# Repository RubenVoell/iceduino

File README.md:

# A ICE40HX4k Breakout for educational purposes

The basic idea behind this project is to create a simple breakout of an ICE40 FPGA with some LEDs and Buttons to interact with the FPGA and enough resources to run a simple softcore, like a small RISC-V core. Therefore a SRAM will be added in case the internal memory blocks are not big enough, The configuration SPI flash may be used to store programm data for the softcore. So this board can be used for teaching basic FPGA, microcontroller and CPU architecture topics.

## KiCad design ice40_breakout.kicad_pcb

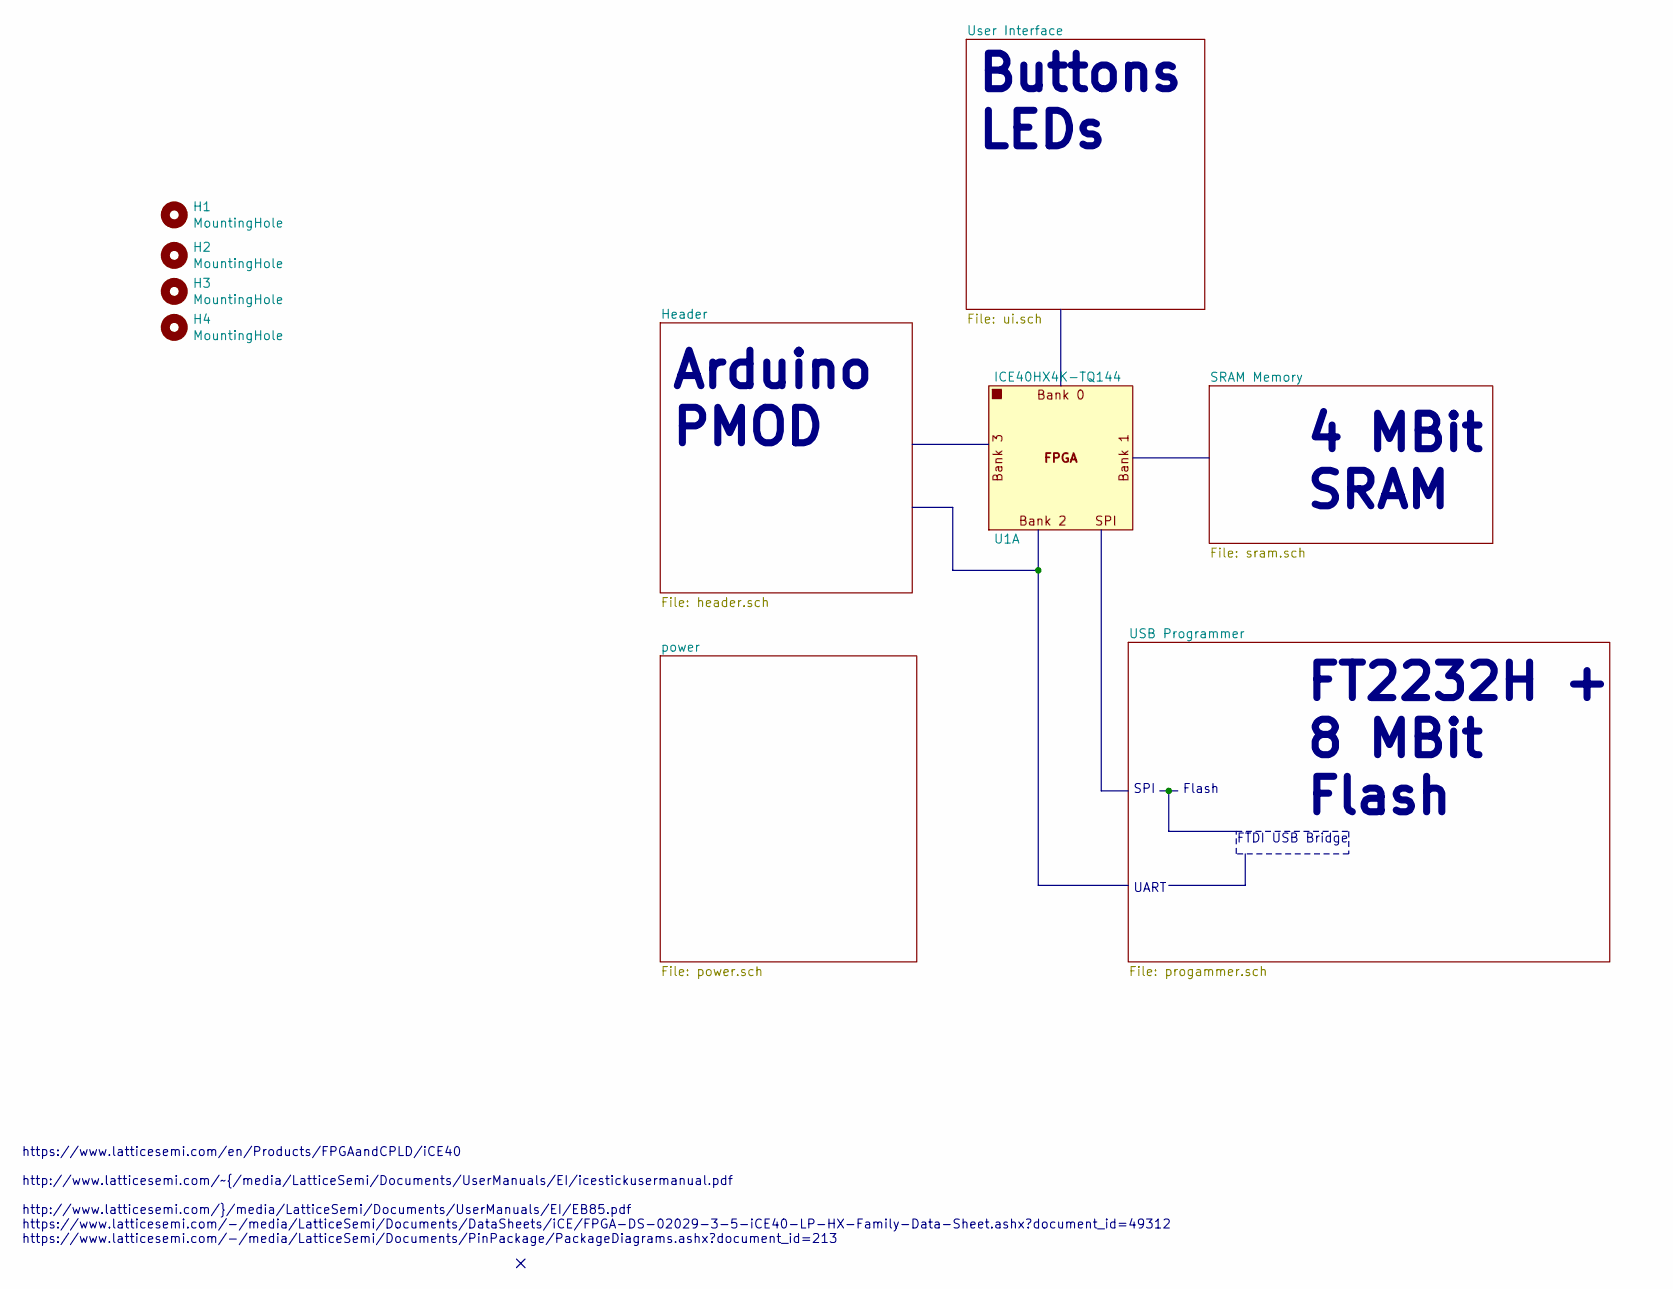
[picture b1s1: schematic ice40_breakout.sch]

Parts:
H1, H2, H3, H4: MountingHole; MountingHole_3mm
U1: ICE40HX4K-TQ144; TQFP-144_20x20mm_P0.5mm; Mfg Part Num ICE40HX4K-TQ144; Digikey 220-1572-ND

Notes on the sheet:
https://www.latticesemi.com/en/Products/FPGAandCPLD/iCE40 http://www.latticesemi.com/~/media/LatticeSemi/Documents/UserManuals/EI/icestickusermanual.pdf http://www.latticesemi.com/~/media/LatticeSemi/Documents/UserManuals/EI/EB85.pdf https://www.latticesemi.com/-/media/LatticeSemi/Documents/DataShe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
SPI
Flash
UART
FTDI USB Bridge
4 MBit SRAM
Arduino PMOD
Buttons LEDs
FT2232H + 8 MBit Flash

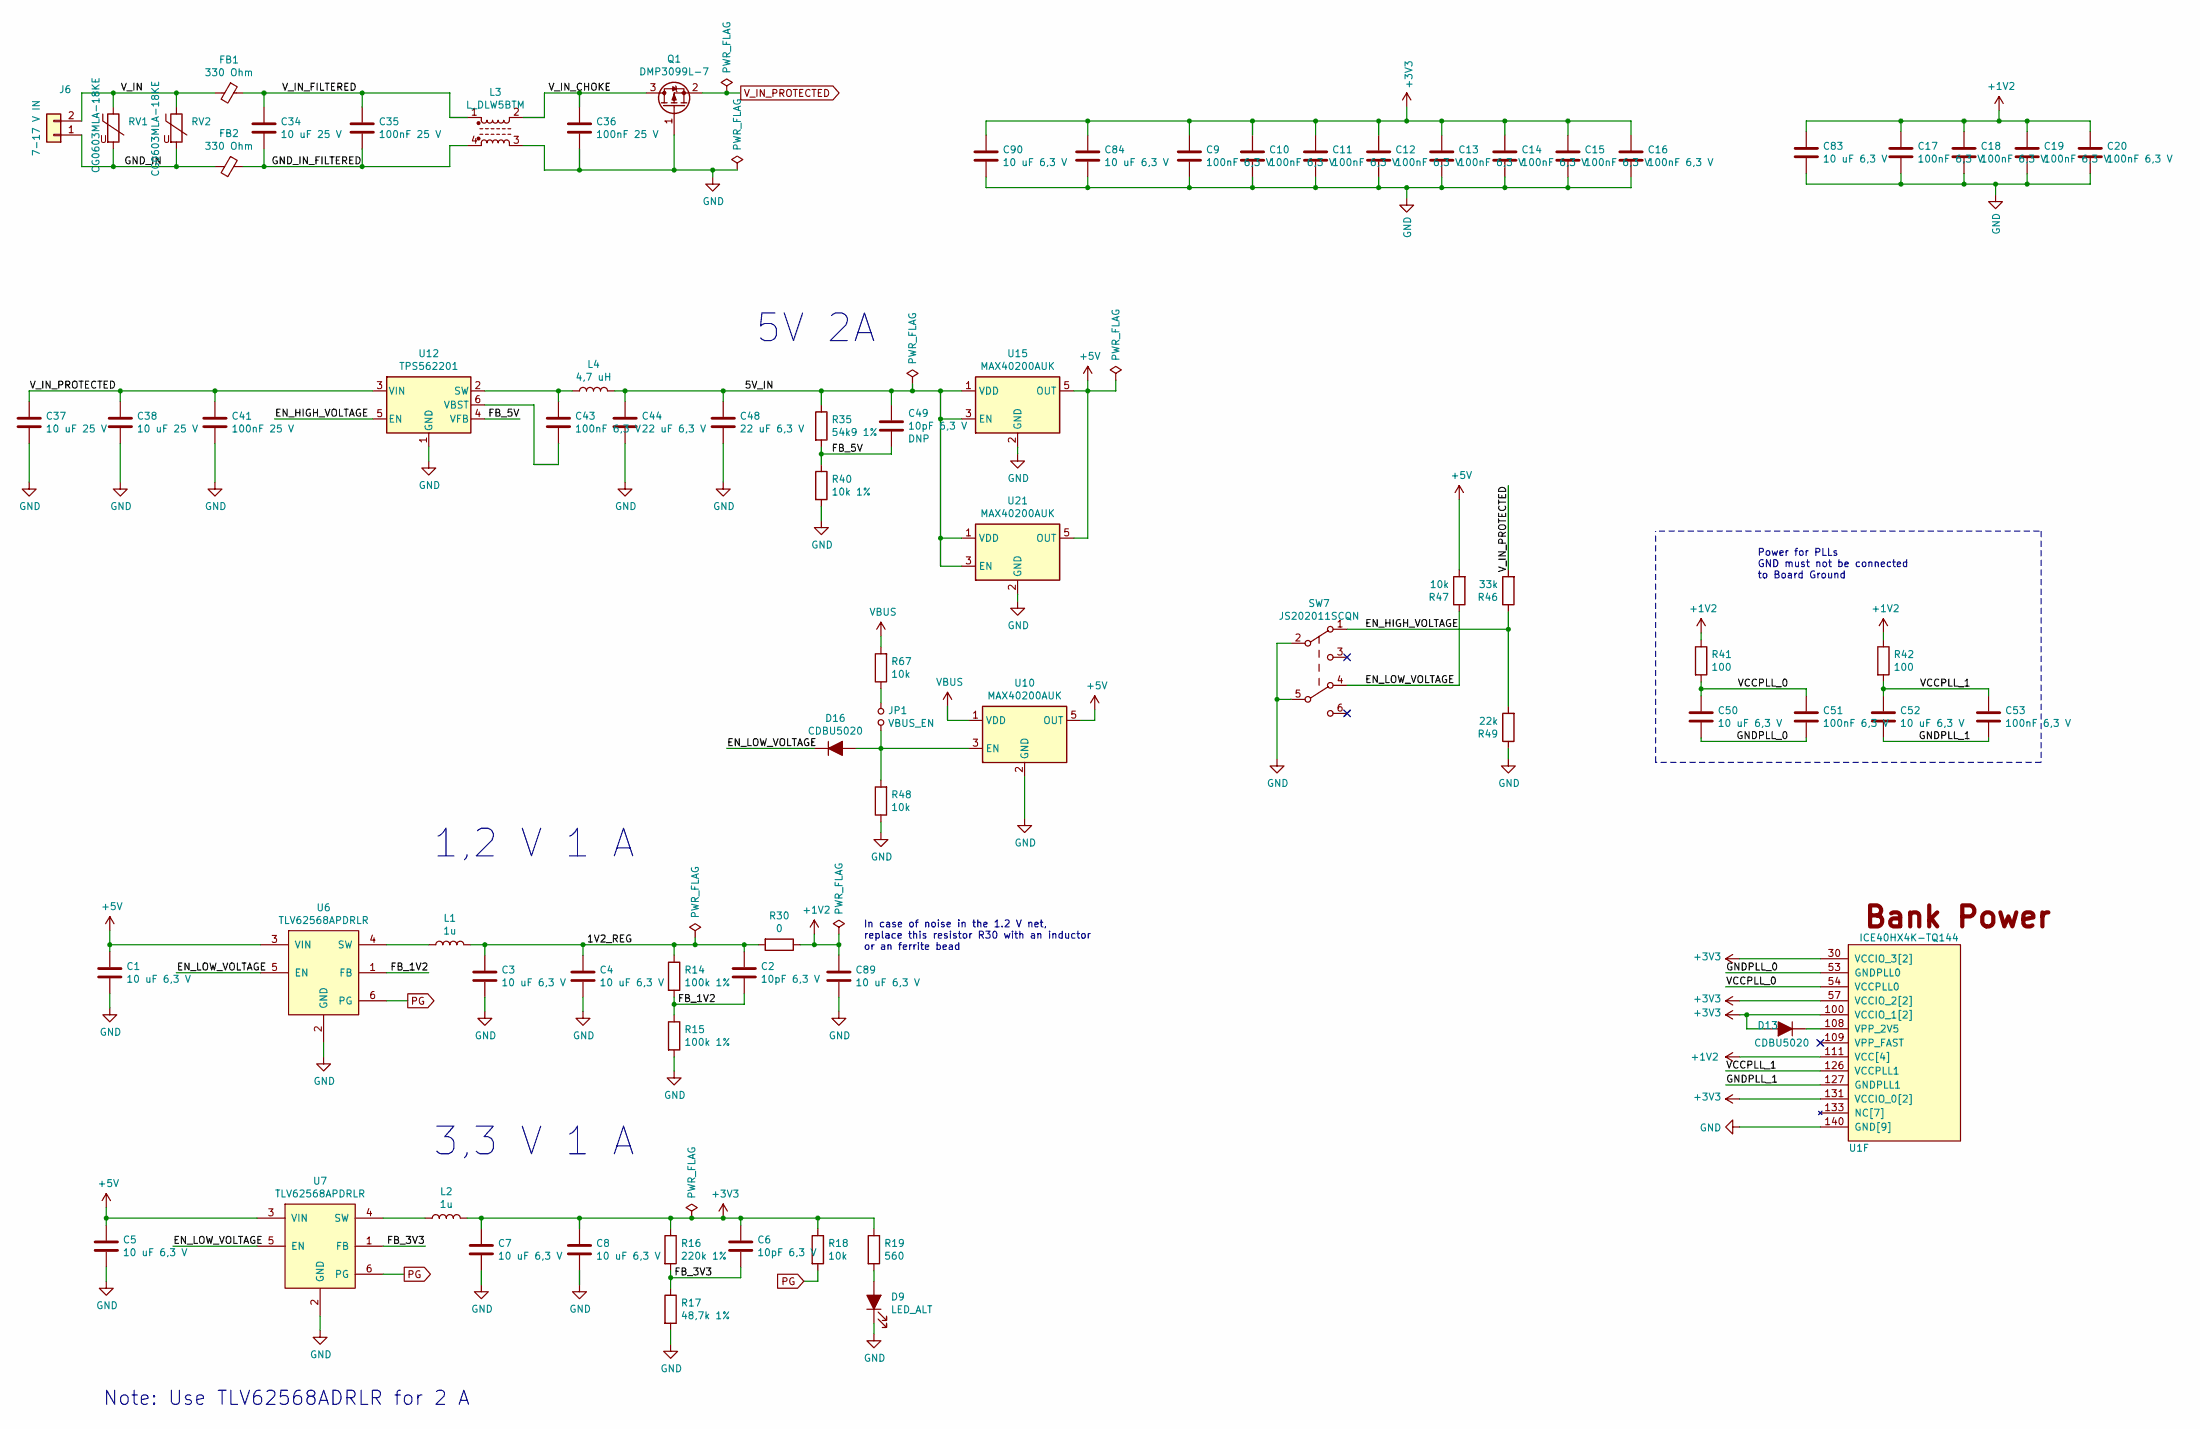
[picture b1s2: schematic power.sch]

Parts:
C1, C3, C4, C5, C7, C8, C50, C52, C83, C84, C89, C90: 10 uF 6,3 V; C_0603_1608Metric; Mfg Part Num CL10A106MQ8NNNC; Digikey 1276-1119-1-ND
C2, C6, C49: 10pF 6,3 V; C_0603_1608Metric; Mfg Part Num CL10C100JB8NNNC; Digikey 1276-1027-1-ND
C9, C10, C11, C12, C13, C14, C15, C16, C17, C18, C19, C20, C43, C51, C53: 100nF 6,3 V; C_0603_1608Metric; Mfg Part Num CL10B104KB8NNNC; Digikey 1276-1000-1-ND
C34, C37, C38: 10 uF 25 V; C_0805_2012Metric; Mfg Part Num CL21A106KAYNNNE; Digikey 1276-2891-1-ND
C35, C36, C41: 100nF 25 V; C_0603_1608Metric; Mfg Part Num CL10B104KB8NNNC; Digikey 1276-1000-1-ND
C44, C48: 22 uF 6,3 V; C_0603_1608Metric; Mfg Part Num GRM188R60J226MEA0D; Digikey 490-7611-1-ND
D9: LED_ALT; LED_0603_1608Metric
D13, D16: CDBU5020; D_0603_1608Metric; Mfg Part Num CDBU0520; Digikey 641-1332-1-ND
FB1, FB2: 330 Ohm; R_0805_2012Metric; Mfg Part Num MPZ2012S331AT000; Digikey 445-1569-1-ND
J6: 7-17 V IN; TerminalBlock_bornier-2_P5.08mm; Mfg Part Num TB007-508-02BE; Digikey 102-6203-ND
JP1: VBUS_EN; PinHeader_1x02_P2.54mm_Vertical
L1, L2: 1u; L_1008_2520Metric_2.5x2mm_footprint; Mfg Part Num MAMK2520T1R0M; Digikey 587-3225-1-ND
L3: L_DLW5BTM; L_Murata_DLW5BTM_5.00x5.00mm_footprint; Mfg Part Num DLW5BTM251SQ2L; Digikey 490-11111-1-ND
L4: 4,7 uH; L_Taiyo-Yuden_NR-50xx; Mfg Part Num NR5040T4R7N; Digikey 587-2373-1-ND
Q1: DMP3099L-7; SOT-23; Mfg Part Num DMP3099L-7; Digikey DMP3099L-7DICT-ND
R14, R15: 100k 1%; R_0603_1608Metric
R16: 220k 1%; R_0603_1608Metric
R17: 48,7k 1%; R_0603_1608Metric
R18, R47, R48, R67: 10k; R_0603_1608Metric
R19: 560; R_0603_1608Metric
R30: 0; R_0805_2012Metric
R35: 54k9 1%; R_0603_1608Metric
R40: 10k 1%; R_0603_1608Metric
R41, R42: 100; R_0603_1608Metric
R46: 33k; R_0603_1608Metric
R49: 22k; R_0603_1608Metric
RV1, RV2: CG0603MLA-18KE; R_0603_1608Metric; Mfg Part Num CG0603MLA-18KE; Digikey CG0603MLA-18KECT-ND
SW7: JS202011SCQN; SW_SLIDE_DPDT_Slide_CK_JS202011SCQN_W3mm_P2.5mm_footprint; Mfg Part Num JS202011SCQN; Digikey 401-2002-1-ND
U1: ICE40HX4K-TQ144; Mfg Part Num ICE40HX4K-TQ144; Digikey 220-1572-ND
U6, U7: TLV62568APDRLR; Texas_DRL_SOT-563_1.6x1.6mm_0.5mm-pitch_footprint; Mfg Part Num TLV62568APDRLR; Digikey 296-51691-1-ND
U10, U15, U21: MAX40200AUK; SOT-23-5; Mfg Part Num MAX40200AUK+T; Digikey MAX40200AUK+TCT-ND
U12: TPS562201; SOT-23-6; Mfg Part Num TPS562201DDCR; Digikey 296-44397-1-ND

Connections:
+1V2: C17.1, C18.1, C19.1, C20.1, C83.1, C89.1, R30.1, R41.1, R42.1, U1.27 (VCC), U1.40 (VCC), U1.92 (VCC), U1.111 (VCC[4])
+3V3: C6.1, C7.1, C8.1, C9.1, C10.1, C11.1, C12.1, C13.1, C14.1, C15.1, C16.1, C84.1, C90.1, D13.2 (A), L2.2, R16.1, R18.1, R19.1, U1.6 (VCCIO_3), U1.30 (VCCIO_3[2]), U1.46 (VCCIO_2), U1.57 (VCCIO_2[2]), U1.89 (VCCIO_1), U1.100 (VCCIO_1[2]), U1.123 (VCCIO_0), U1.131 (VCCIO_0[2]); also elsewhere on the board
+5V: C1.1, C5.1, R47.2, U6.3 (VIN), U7.3 (VIN), U10.5 (OUT), U15.5 (OUT), U21.5 (OUT); also elsewhere on the board
/power/1V2_REG: C2.1, C3.1, C4.1, L1.2, R14.1, R30.2
/power/5V_IN: C44.1, C48.1, C49.1, L4.2, R35.1, U15.1 (VDD), U15.3 (EN), U21.1 (VDD), U21.3 (EN)
/power/EN_HIGH_VOLTAGE: R46.1, R49.2, SW7.1 (A), U12.5 (EN)
/power/EN_LOW_VOLTAGE: D16.1 (K), R47.1, SW7.4 (A), U6.5 (EN), U7.5 (EN)
/power/FB_1V2: C2.2, R14.2, R15.1, U6.1 (FB)
/power/FB_3V3: C6.2, R16.2, R17.1, U7.1 (FB)
/power/FB_5V: C49.2, R35.2, R40.1, U12.4 (VFB)
/power/GNDPLL_0: C50.2, C51.2, U1.53 (GNDPLL0)
/power/GNDPLL_1: C52.2, C53.2, U1.127 (GNDPLL1)
/power/GND_IN: FB2.2, J6.1, RV1.2, RV2.2
/power/GND_IN_FILTERED: C34.2, C35.2, FB2.1, L3.4
/power/VCCPLL_0: C50.1, C51.1, R41.2, U1.54 (VCCPLL0)
/power/VCCPLL_1: C52.1, C53.1, R42.2, U1.126 (VCCPLL1)
/power/V_IN: FB1.2, J6.2, RV1.1, RV2.1
/power/V_IN_CHOKE: C36.1, L3.2, Q1.3 (D)
/power/V_IN_FILTERED: C34.1, C35.1, FB1.1, L3.1
CRESET_B: R18.2, U6.6 (PG), U7.6 (PG); also elsewhere on the board
GND: C1.2, C3.2, C4.2, C5.2, C7.2, C8.2, C9.2, C10.2, C11.2, C12.2, C13.2, C14.2, C15.2, C16.2, C17.2, C18.2, C19.2, C20.2, C36.2, C37.2, C38.2, C41.2, C44.2, C48.2, C83.2, C84.2, C89.2, C90.2, D9.1 (K), L3.3, Q1.1 (G), R15.2, R17.2, R40.2, R48.1, R49.1, SW7.2 (B), SW7.5 (B), U1.5 (GND), U1.13 (GND), U1.14 (GND), U1.59 (GND), U1.69 (GND), U1.86 (GND), U1.103 (GND), U1.132 (GND), U1.140 (GND[9]), U6.2 (GND), U7.2 (GND), U10.2 (GND), U12.1 (GND), U15.2 (GND), U21.2 (GND); also elsewhere on the board
unnamed: C43.1, L4.1, U12.2 (SW)
unnamed: C43.2, U12.6 (VBST)
unnamed: D9.2 (A), R19.2
unnamed: D13.1 (K), U1.108 (VPP_2V5)
unnamed: D16.2 (A), JP1.2, R48.2, U10.3 (EN)
unnamed: JP1.1, R67.1
unnamed: L1.1, U6.4 (SW)
unnamed: L2.1, U7.4 (SW)
unnamed: U1.35 (NC), U1.36 (NC), U1.50 (NC), U1.51 (NC), U1.58 (NC), U1.77 (NC), U1.133 (NC[7])
VBUS: R67.2, U10.1 (VDD); also elsewhere on the board
V_IN_PROTECTED: C37.1, C38.1, C41.1, Q1.2 (S), R46.2, U12.3 (VIN); also elsewhere on the board

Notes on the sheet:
3,3 V 1 A
Power for PLLs GND must not be connected to Board Ground
In case of noise in the 1.2 V net, replace this resistor R30 with an inductor or an ferrite bead
5V 2A
Note: Use TLV62568ADRLR for 2 A
1,2 V 1 A

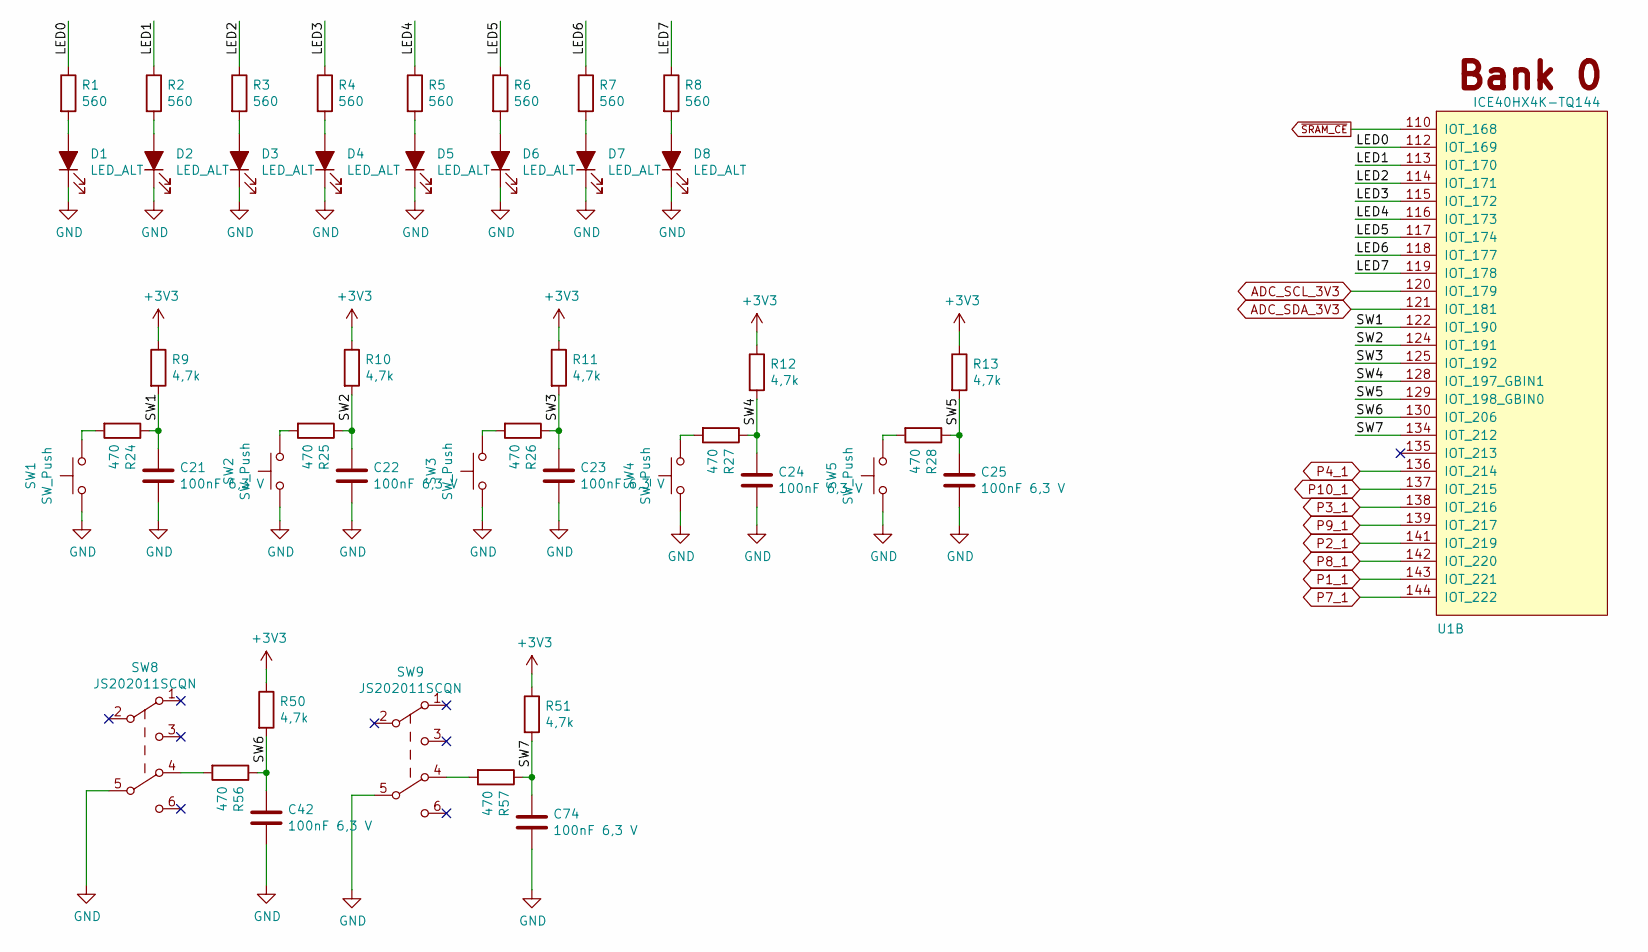
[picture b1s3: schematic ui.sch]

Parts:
C21, C22, C23, C24, C25, C42, C74: 100nF 6,3 V; C_0603_1608Metric; Mfg Part Num CL10B104KB8NNNC; Digikey 1276-1000-1-ND
D1, D2, D3, D4, D5, D6, D7, D8: LED_ALT; LED_0603_1608Metric
R1, R2, R3, R4, R5, R6, R7, R8: 560; R_0603_1608Metric
R9, R10, R11, R12, R13, R50, R51: 4,7k; R_0603_1608Metric
R24, R25, R26, R27, R28, R56, R57: 470; R_0603_1608Metric
SW1, SW2, SW3, SW4, SW5: SW_Push; SW_SPST_TL3305A; Mfg Part Num TL3305AF160QG; Digikey EG5350CT-ND
SW8, SW9: JS202011SCQN; SW_SLIDE_DPDT_Slide_CK_JS202011SCQN_W3mm_P2.5mm_footprint; Mfg Part Num JS202011SCQN; Digikey 401-2002-1-ND
U1: ICE40HX4K-TQ144; Mfg Part Num ICE40HX4K-TQ144; Digikey 220-1572-ND

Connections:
+3V3: R9.1, R10.1, R11.1, R12.1, R13.1, R50.1, R51.1; also elsewhere on the board
/User Interface/LED0: R1.1, U1.112 (IOT_169)
/User Interface/LED1: R2.1, U1.113 (IOT_170)
/User Interface/LED2: R3.1, U1.114 (IOT_171)
/User Interface/LED3: R4.1, U1.115 (IOT_172)
/User Interface/LED4: R5.1, U1.116 (IOT_173)
/User Interface/LED5: R6.1, U1.117 (IOT_174)
/User Interface/LED6: R7.1, U1.118 (IOT_177)
/User Interface/LED7: R8.1, U1.119 (IOT_178)
/User Interface/SW1: C21.1, R9.2, R24.1, U1.122 (IOT_190)
/User Interface/SW2: C22.1, R10.2, R25.1, U1.124 (IOT_191)
/User Interface/SW3: C23.1, R11.2, R26.1, U1.125 (IOT_192)
/User Interface/SW4: C24.1, R12.2, R27.1, U1.128 (IOT_197_GBIN1)
/User Interface/SW5: C25.1, R13.2, R28.1, U1.129 (IOT_198_GBIN0)
/User Interface/SW6: C42.1, R50.2, R56.1, U1.130 (IOT_206)
/User Interface/SW7: C74.1, R51.2, R57.1, U1.134 (IOT_212)
ADC_SCL_3V3: U1.120 (IOT_179); also elsewhere on the board
ADC_SDA_3V3: U1.121 (IOT_181); also elsewhere on the board
GND: C21.2, C22.2, C23.2, C24.2, C25.2, C42.2, C74.2, D1.1 (K), D2.1 (K), D3.1 (K), D4.1 (K), D5.1 (K), D6.1 (K), D7.1 (K), D8.1 (K), SW1.1, SW2.1, SW3.1, SW4.1, SW5.1, SW8.5 (B), SW9.5 (B); also elsewhere on the board
unnamed: D1.2 (A), R1.2
unnamed: D2.2 (A), R2.2
unnamed: D3.2 (A), R3.2
unnamed: D4.2 (A), R4.2
unnamed: D5.2 (A), R5.2
unnamed: D6.2 (A), R6.2
unnamed: D7.2 (A), R7.2
unnamed: D8.2 (A), R8.2
unnamed: R24.2, SW1.2
unnamed: R25.2, SW2.2
unnamed: R26.2, SW3.2
unnamed: R27.2, SW4.2
unnamed: R28.2, SW5.2
unnamed: R56.2, SW8.4 (A)
unnamed: R57.2, SW9.4 (A)
P1_1: U1.143 (IOT_221); also elsewhere on the board
P2_1: U1.141 (IOT_219); also elsewhere on the board
P3_1: U1.138 (IOT_216); also elsewhere on the board
P4_1: U1.136 (IOT_214); also elsewhere on the board
P7_1: U1.144 (IOT_222); also elsewhere on the board
P8_1: U1.142 (IOT_220); also elsewhere on the board
P9_1: U1.139 (IOT_217); also elsewhere on the board
P10_1: U1.137 (IOT_215); also elsewhere on the board
~SRAM_CE~: U1.110 (IOT_168); also elsewhere on the board

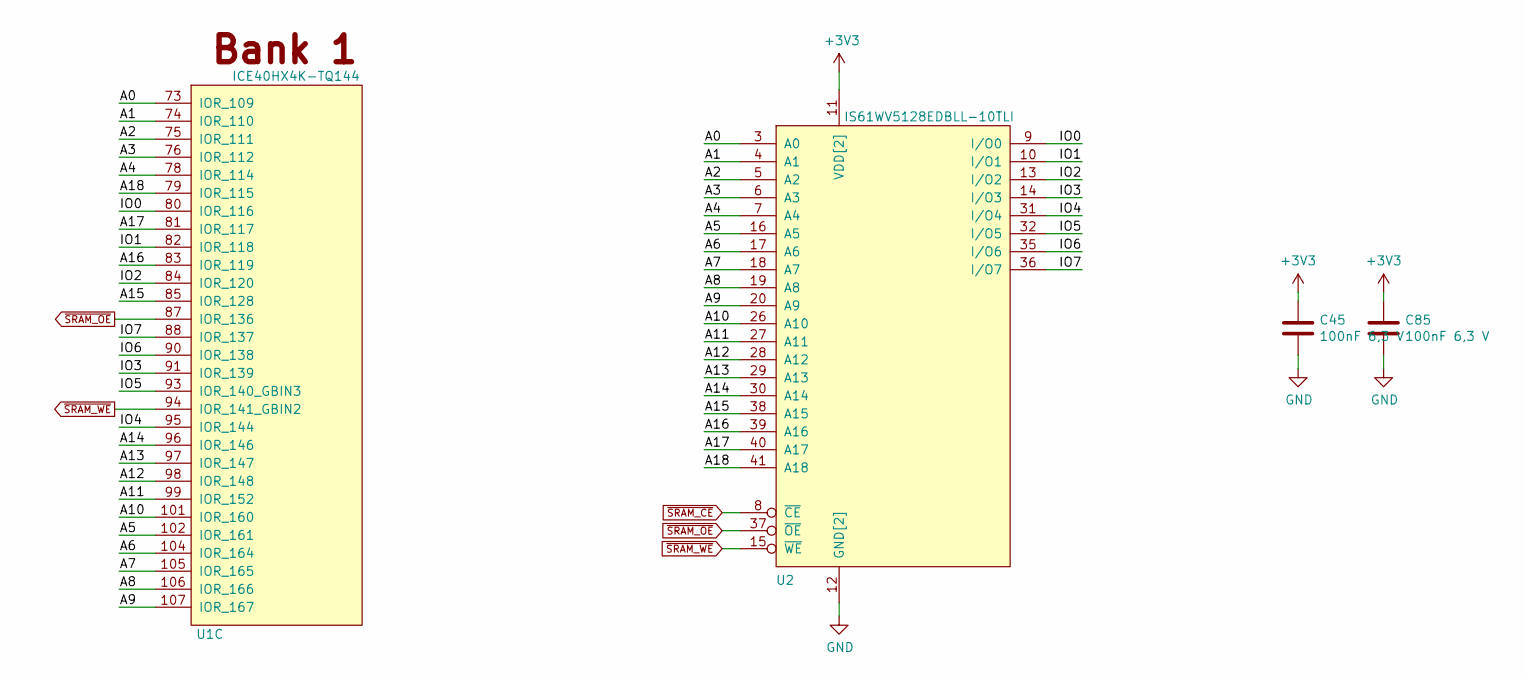
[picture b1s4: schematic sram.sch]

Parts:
C45, C85: 100nF 6,3 V; C_0603_1608Metric; Mfg Part Num CL10B104KB8NNNC; Digikey 1276-1000-1-ND
U1: ICE40HX4K-TQ144; Mfg Part Num ICE40HX4K-TQ144; Digikey 220-1572-ND
U2: IS61WV5128EDBLL-10TLI; TSOP-II-44_10.16x18.41mm_P0.8mm; Mfg Part Num IS61WV5128EDBLL-10TLI; Digikey 706-1147-ND

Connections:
+3V3: C45.1, C85.1, U2.11 (VDD[2]), U2.33 (VDD); also elsewhere on the board
/SRAM Memory/A0: U1.73 (IOR_109), U2.3 (A0)
/SRAM Memory/A1: U1.74 (IOR_110), U2.4 (A1)
/SRAM Memory/A2: U1.75 (IOR_111), U2.5 (A2)
/SRAM Memory/A3: U1.76 (IOR_112), U2.6 (A3)
/SRAM Memory/A4: U1.78 (IOR_114), U2.7 (A4)
/SRAM Memory/A5: U1.102 (IOR_161), U2.16 (A5)
/SRAM Memory/A6: U1.104 (IOR_164), U2.17 (A6)
/SRAM Memory/A7: U1.105 (IOR_165), U2.18 (A7)
/SRAM Memory/A8: U1.106 (IOR_166), U2.19 (A8)
/SRAM Memory/A9: U1.107 (IOR_167), U2.20 (A9)
/SRAM Memory/A10: U1.101 (IOR_160), U2.26 (A10)
/SRAM Memory/A11: U1.99 (IOR_152), U2.27 (A11)
/SRAM Memory/A12: U1.98 (IOR_148), U2.28 (A12)
/SRAM Memory/A13: U1.97 (IOR_147), U2.29 (A13)
/SRAM Memory/A14: U1.96 (IOR_146), U2.30 (A14)
/SRAM Memory/A15: U1.85 (IOR_128), U2.38 (A15)
/SRAM Memory/A16: U1.83 (IOR_119), U2.39 (A16)
/SRAM Memory/A17: U1.81 (IOR_117), U2.40 (A17)
/SRAM Memory/A18: U1.79 (IOR_115), U2.41 (A18)
/SRAM Memory/IO0: U1.80 (IOR_116), U2.9 (I/O0)
/SRAM Memory/IO1: U1.82 (IOR_118), U2.10 (I/O1)
/SRAM Memory/IO2: U1.84 (IOR_120), U2.13 (I/O2)
/SRAM Memory/IO3: U1.91 (IOR_139), U2.14 (I/O3)
/SRAM Memory/IO4: U1.95 (IOR_144), U2.31 (I/O4)
/SRAM Memory/IO5: U1.93 (IOR_140_GBIN3), U2.32 (I/O5)
/SRAM Memory/IO6: U1.90 (IOR_138), U2.35 (I/O6)
/SRAM Memory/IO7: U1.88 (IOR_137), U2.36 (I/O7)
GND: C45.2, C85.2, U2.12 (GND[2]), U2.34 (GND); also elsewhere on the board
~SRAM_CE~: U2.8 (~CE~); also elsewhere on the board
~SRAM_OE~: U1.87 (IOR_136), U2.37 (~OE~)
~SRAM_WE~: U1.94 (IOR_141_GBIN2), U2.15 (~WE~)

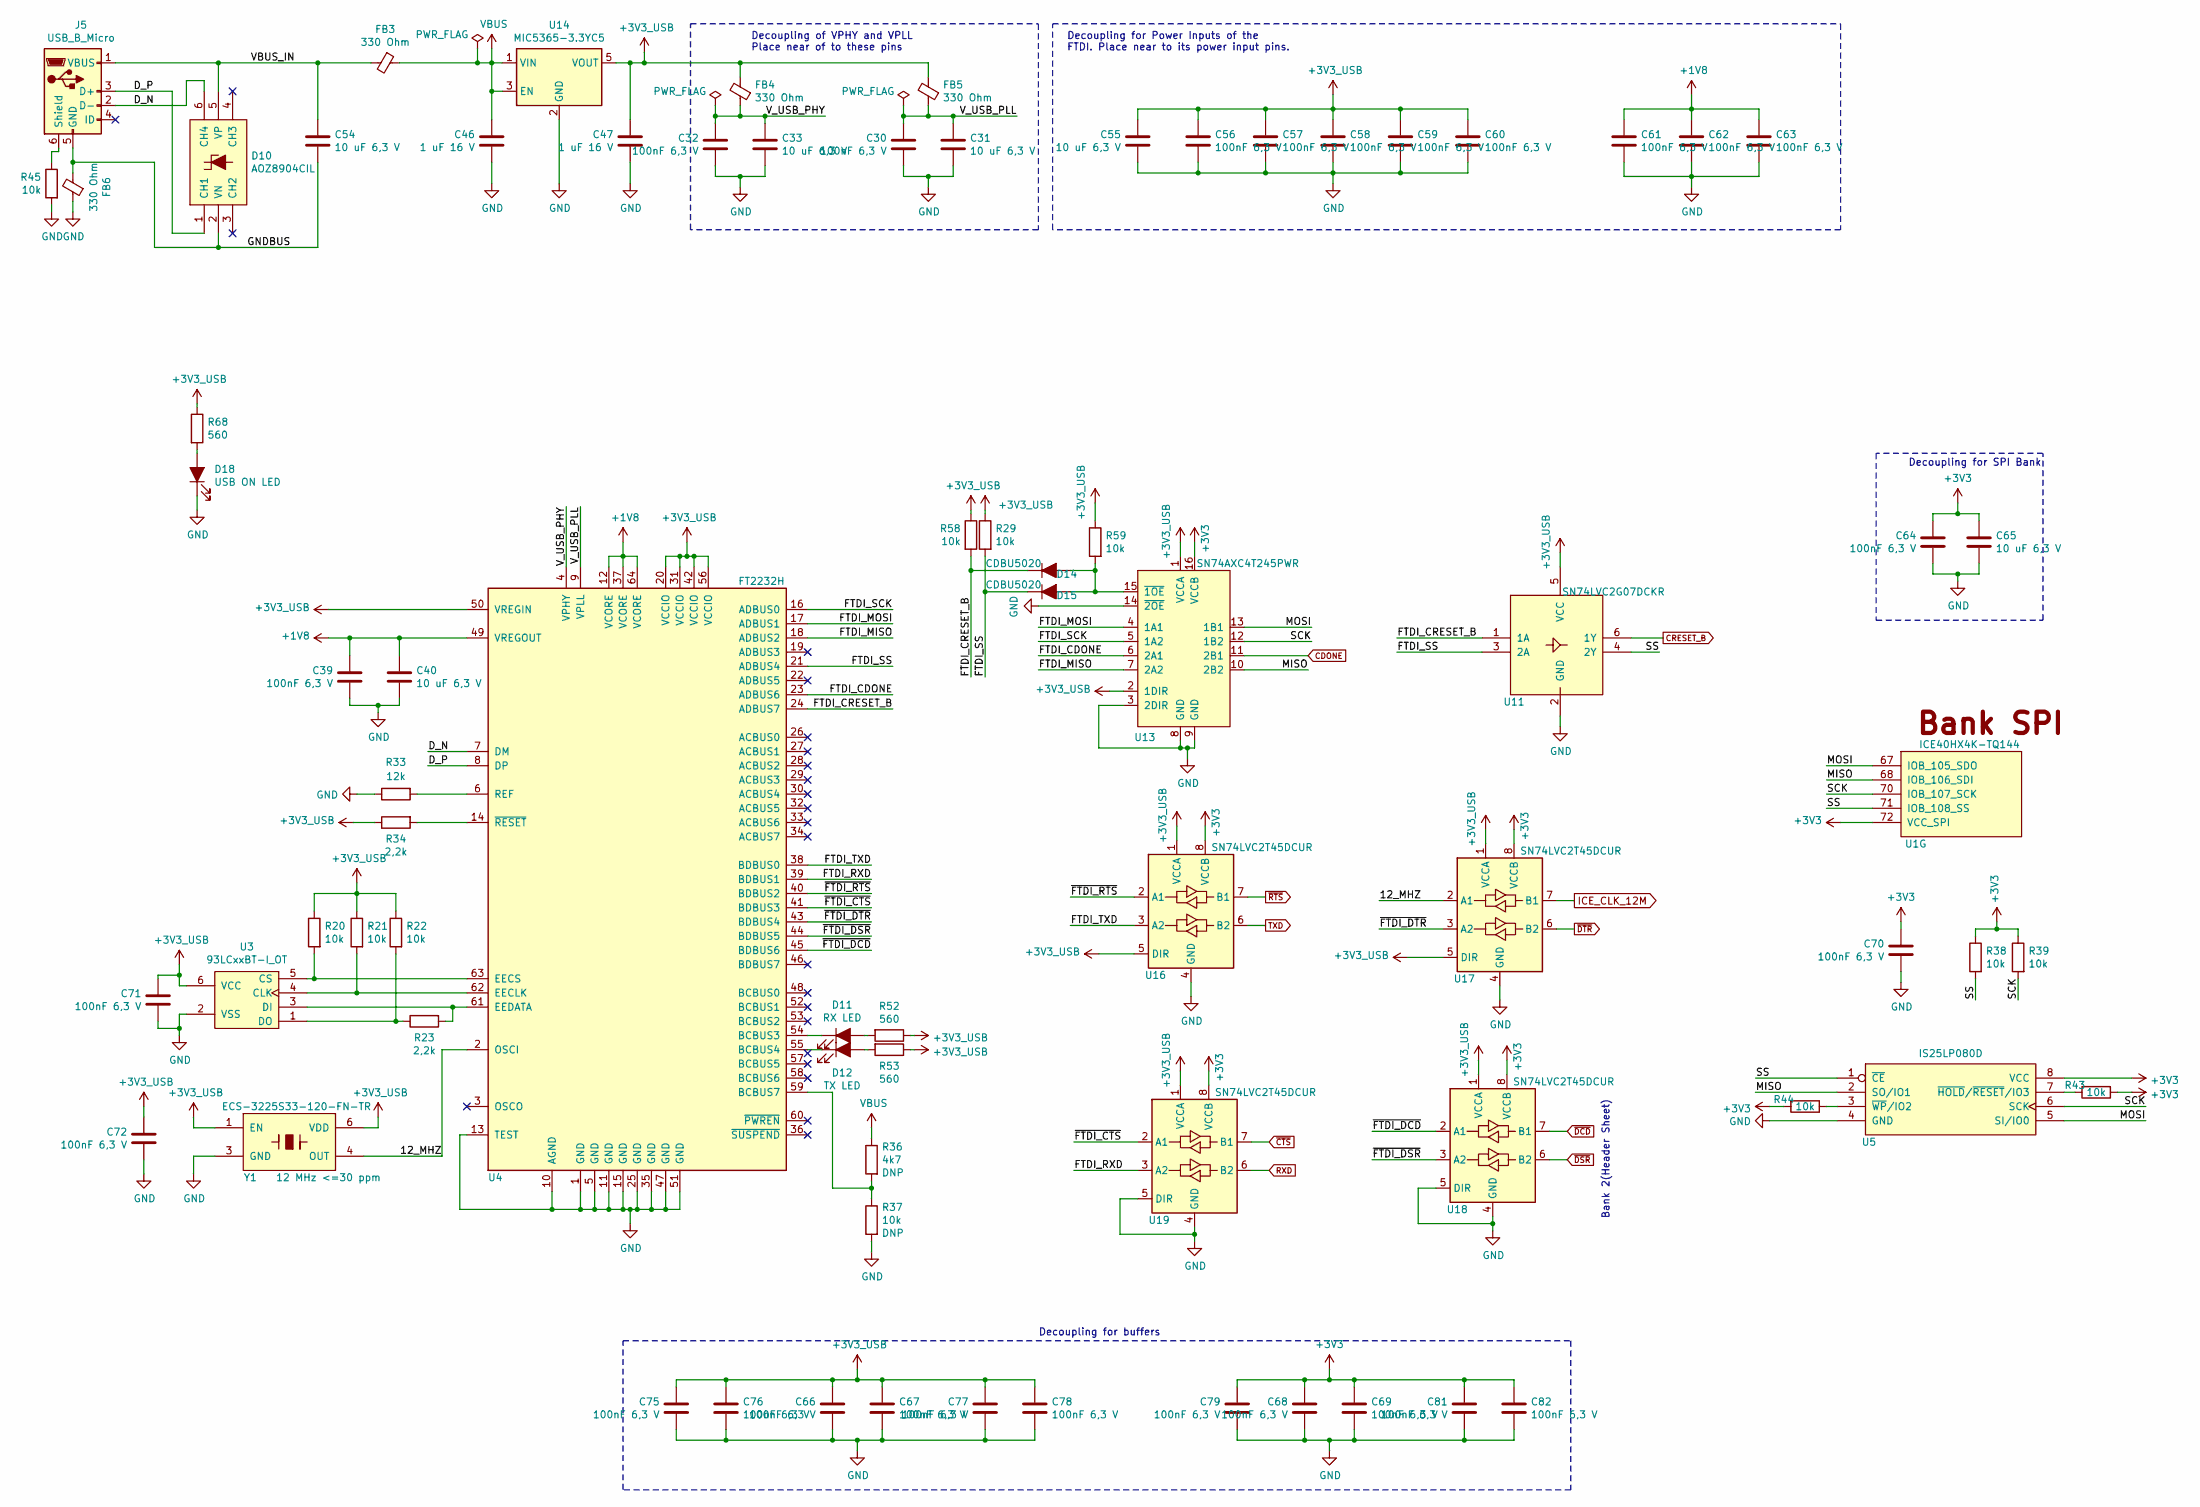
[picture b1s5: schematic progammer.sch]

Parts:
C30, C32, C39, C56, C57, C58, C59, C60, C61, C62, C63, C64, C66, C67, C68, C69, C70, C71, C72, C75, C76, C77, C78, C79, C81, C82: 100nF 6,3 V; C_0603_1608Metric; Mfg Part Num CL10B104KB8NNNC; Digikey 1276-1000-1-ND
C31, C33, C40, C54, C55, C65: 10 uF 6,3 V; C_0603_1608Metric; Mfg Part Num CL10A106MQ8NNNC; Digikey 1276-1119-1-ND
C46, C47: 1 uF 16 V; C_0603_1608Metric; Mfg Part Num CL10B105MO8NNWC; Digikey 1276-6524-1-ND
D10: AOZ8904CIL; SOT-23-6; Mfg Part Num AOZ8904CIL; Digikey 785-1755-1-ND
D11: RX LED; LED_0603_1608Metric
D12: TX LED; LED_0603_1608Metric
D14, D15: CDBU5020; D_0603_1608Metric; Mfg Part Num CDBU0520; Digikey 641-1332-1-ND
D18: USB ON LED; LED_0603_1608Metric
FB3, FB4, FB5, FB6: 330 Ohm; R_0805_2012Metric; Mfg Part Num MPZ2012S331AT000; Digikey 445-1569-1-ND
J5: USB_B_Micro; Amphenol_microUSB_B_footprint; Mfg Part Num 10118194-0001LF; Digikey 609-4618-1-ND
R20, R21, R22, R29, R37, R38, R39, R43, R44, R45, R58, R59: 10k; R_0603_1608Metric
R23, R34: 2,2k; R_0603_1608Metric
R33: 12k; R_0603_1608Metric
R36: 4k7; R_0603_1608Metric
R52, R53, R68: 560; R_0603_1608Metric
U1: ICE40HX4K-TQ144; Mfg Part Num ICE40HX4K-TQ144; Digikey 220-1572-ND
U3: 93LCxxBT-I_OT; SOT-23-6; Mfg Part Num 93LC56BT-I/OT; Digikey 93LC56BT-I/OTCT-ND
U4: FT2232H; LQFP-64_10x10mm_P0.5mm; Mfg Part Num FT2232HL-REEL; Digikey 768-1024-1-ND
U5: IS25LP080D; SO-8_3.9x4.9mm_P1.27mm; Mfg Part Num IS25LP080D-JNLE; Digikey 706-1580-ND
U11: SN74LVC2G07DCKR; SOT-363_SC-70-6; Mfg Part Num SN74LVC2G07DCKR; Digikey 296-13495-1-ND
U13: SN74AXC4T245PWR; TSSOP-16_4.4x5mm_P0.65mm; Mfg Part Num SN74AXC4T245PWR; Digikey 296-53472-1-ND
U14: MIC5365-3.3YC5; SOT-353_SC-70-5; Mfg Part Num MIC5365-3.3YC5-TR; Digikey 576-3193-1-ND
U16, U17, U18, U19: SN74LVC2T45DCUR; VSSOP-8_2.4x2.1mm_P0.5mm; Mfg Part Num SN74LVC2T45DCUR; Digikey 296-17014-1-ND
Y1: ECS-3225S33-120-FN-TR; Y_ECS-3225S_3.2x2.5mm_footprint; Mfg Part Num ECS-3225S33-120-FN-TR; Digikey XC2217CT-ND

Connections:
+1V8: C39.1, C40.1, C61.1, C62.1, C63.1, U4.12 (VCORE), U4.37 (VCORE), U4.49 (VREGOUT), U4.64 (VCORE)
+3V3: C64.1, C65.1, C68.1, C69.1, C70.1, C79.1, C81.1, C82.1, R38.1, R39.1, R43.2, R44.2, U1.72 (VCC_SPI), U5.8 (VCC), U13.16 (VCCB), U16.8 (VCCB), U17.8 (VCCB), U18.8 (VCCB), U19.8 (VCCB); also elsewhere on the board
+3V3_FTDI: C47.1, C55.1, C56.1, C57.1, C58.1, C59.1, C60.1, C66.1, C67.1, C71.1, C72.1, C75.1, C76.1, C77.1, C78.1, FB4.2, FB5.2, R20.1, R21.1, R22.1, R29.1, R34.1, R52.1, R53.1, R58.1, R59.1, R68.1, U3.6 (VCC), U4.20 (VCCIO), U4.31 (VCCIO), U4.42 (VCCIO), U4.50 (VREGIN), U4.56 (VCCIO), U11.5 (VCC), U13.1 (VCCA), U13.2 (1DIR), U14.5 (VOUT), U16.1 (VCCA), U16.5 (DIR), U17.1 (VCCA), U17.5 (DIR), U18.1 (VCCA), U19.1 (VCCA), Y1.1 (EN), Y1.6 (VDD)
/USB Programmer/12_MHZ: U4.2 (OSCI), U17.2 (A1), Y1.4 (OUT)
/USB Programmer/D_N: D10.6 (CH4), J5.2 (D-), U4.7 (DM)
/USB Programmer/D_P: D10.1 (CH1), J5.3 (D+), U4.8 (DP)
/USB Programmer/FTDI_CDONE: U4.23 (ADBUS6), U13.6 (2A1)
/USB Programmer/FTDI_CRESET_B: D14.1 (K), R58.2, U4.24 (ADBUS7), U11.1 (1A)
/USB Programmer/FTDI_MISO: U4.18 (ADBUS2), U13.7 (2A2)
/USB Programmer/FTDI_MOSI: U4.17 (ADBUS1), U13.4 (1A1)
/USB Programmer/FTDI_RXD: U4.39 (BDBUS1), U19.3 (A2)
/USB Programmer/FTDI_SCK: U4.16 (ADBUS0), U13.5 (1A2)
/USB Programmer/FTDI_SS: D15.1 (K), R29.2, U4.21 (ADBUS4), U11.3 (2A)
/USB Programmer/FTDI_TXD: U4.38 (BDBUS0), U16.3 (A2)
/USB Programmer/GNDBUS: C54.2, D10.2 (VN), FB6.2, J5.5 (GND)
/USB Programmer/MISO: U1.68 (IOB_106_SDI), U5.2 (SO/IO1), U13.10 (2B2)
/USB Programmer/MOSI: U1.67 (IOB_105_SDO), U5.5 (SI/IO0), U13.13 (1B1)
/USB Programmer/SCK: R39.2, U1.70 (IOB_107_SCK), U5.6 (SCK), U13.12 (1B2)
/USB Programmer/SS: R38.2, U1.71 (IOB_108_SS), U5.1 (~CE~), U11.4 (2Y)
/USB Programmer/VBUS_IN: C54.1, D10.5 (VP), FB3.2, J5.1 (VBUS)
/USB Programmer/V_USB_PHY: C32.1, C33.1, FB4.1, U4.4 (VPHY)
/USB Programmer/V_USB_PLL: C30.1, C31.1, FB5.1, U4.9 (VPLL)
/USB Programmer/~FTDI_CTS~: U4.41 (BDBUS3), U19.2 (A1)
/USB Programmer/~FTDI_DCD~: U4.45 (BDBUS6), U18.2 (A1)
/USB Programmer/~FTDI_DSR~: U4.44 (BDBUS5), U18.3 (A2)
/USB Programmer/~FTDI_DTR~: U4.43 (BDBUS4), U17.3 (A2)
/USB Programmer/~FTDI_RTS~: U4.40 (BDBUS2), U16.2 (A1)
CDONE: U13.11 (2B1); also elsewhere on the board
CRESET_B: U11.6 (1Y); also elsewhere on the board
GND: C30.2, C31.2, C32.2, C33.2, C39.2, C40.2, C46.2, C47.2, C55.2, C56.2, C57.2, C58.2, C59.2, C60.2, C61.2, C62.2, C63.2, C64.2, C65.2, C66.2, C67.2, C68.2, C69.2, C70.2, C71.2, C72.2, C75.2, C76.2, C77.2, C78.2, C79.2, C81.2, C82.2, D18.1 (K), FB6.1, R33.1, R37.2, R45.2, U3.2 (VSS), U4.1 (GND), U4.5 (GND), U4.10 (AGND), U4.11 (GND), U4.13 (TEST), U4.15 (GND), U4.25 (GND), U4.35 (GND), U4.47 (GND), U4.51 (GND), U5.4 (GND), U11.2 (GND), U13.3 (2DIR), U13.8 (GND), U13.9 (GND), U13.14 (~2OE~), U14.2 (GND), U16.4 (GND), U17.4 (GND), U18.4 (GND), U18.5 (DIR), U19.4 (GND), U19.5 (DIR), Y1.3 (GND); also elsewhere on the board
ICE_CLK_12M: U17.7 (B1); also elsewhere on the board
unnamed: D11.1 (K), U4.54 (BCBUS3)
unnamed: D11.2 (A), R52.2
unnamed: D12.1 (K), U4.55 (BCBUS4)
unnamed: D12.2 (A), R53.2
unnamed: D14.2 (A), D15.2 (A), R59.2, U13.15 (~1OE~)
unnamed: D18.2 (A), R68.2
unnamed: J5.6 (Shield), R45.1
unnamed: R20.2, U3.5 (CS), U4.63 (EECS)
unnamed: R21.2, U3.4 (CLK), U4.62 (EECLK)
unnamed: R22.2, R23.1, U3.1 (DO)
unnamed: R23.2, U3.3 (DI), U4.61 (EEDATA)
unnamed: R33.2, U4.6 (REF)
unnamed: R34.2, U4.14 (~RESET)
unnamed: R36.2, R37.1, U4.59 (BCBUS7)
unnamed: R43.1, U5.7 (~HOLD~/~RESET~/IO3)
unnamed: R44.1, U5.3 (~WP~/IO2)
RXD: U19.6 (B2); also elsewhere on the board
TXD: U16.6 (B2); also elsewhere on the board
VBUS: C46.1, FB3.1, R36.1, U14.1 (VIN), U14.3 (EN); also elsewhere on the board
~CTS~: U19.7 (B1); also elsewhere on the board
~DCD~: U18.7 (B1); also elsewhere on the board
~DSR~: U18.6 (B2); also elsewhere on the board
~DTR~: U17.6 (B2); also elsewhere on the board
~RTS~: U16.7 (B1); also elsewhere on the board

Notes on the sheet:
Decoupling of VPHY and VPLL Place near of to these pins
Bank 2(Header Sheet)
Decoupling for Power Inputs of the FTDI. Place near to its power input pins.
Decoupling for buffers
Decoupling for SPI Bank
